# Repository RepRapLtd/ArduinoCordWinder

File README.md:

An Arduino-controlled cord winder for moving things.

(Original application - release chickens from their coop at dawn.)

This consists of a laser-cut box held together with 3D pronted parts.  Inside is a cylindrical winder driven by a geared motor.  These are controlled by an Arduino Uno with a shield that drives the motor.

As distributed it is powered by 12 volts, and takes an opto-isolated input from a solar cell (assumed also to be charging the 12 volt battery).  When the solar voltage rises above a threshold the winder runs until a marker on the wound cord triggers a microswitch, causing it to stop.

There are also push buttons to wind and unwind the cord manually.

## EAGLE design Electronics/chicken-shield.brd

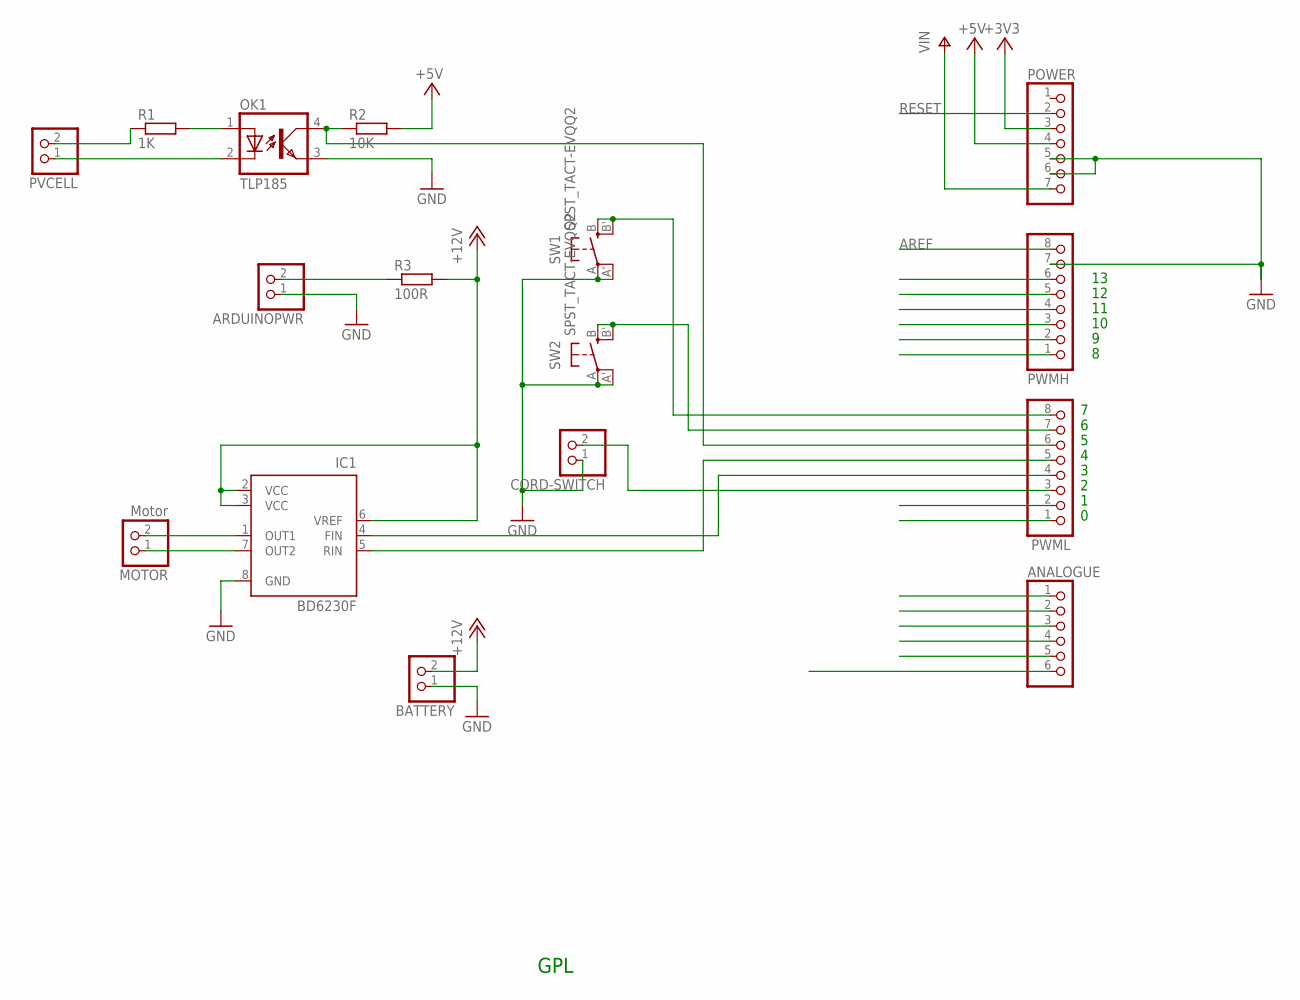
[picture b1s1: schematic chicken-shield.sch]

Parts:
ANALOGUE: PINHD-1X6; 1X06
ARDUINOPWR: PINHD-1X2; 1X02
BATTERY: PINHD-1X2; 1X02
CORD-SWITCH: PINHD-1X2; 1X02
IC1: BD6230F; SOP8
MOTOR: Motor; 1X02
OK1: TLP185; MINI-FLAT-4
POWER: PINHD-1X7; 1X07
PVCELL: PINHD-1X2; 1X02
PWMH: PINHD-1X8; 1X08
PWML: PINHD-1X8; 1X08
R1: 1K; M0805
R2: 10K; M0805
R3: 100R; 0204/7
SW1, SW2: SPST_TACT-EVQQ2; EVQ-Q2

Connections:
+3V3: POWER.3
+5V: POWER.4, R2.2
+12V: BATTERY.2, IC1.2 (VCC), IC1.3 (VCC), IC1.6 (VREF), R3.2
A0: ANALOGUE.1
A1: ANALOGUE.2
A2: ANALOGUE.3
A3: ANALOGUE.4
A4: ANALOGUE.5
A5: ANALOGUE.6
AREF: PWMH.8
DIG0_RX: PWML.1
DIG1_TX: PWML.2
DIG2: IC1.5 (RIN), PWML.5
DIG3: IC1.4 (FIN), PWML.4
DIG4: CORD-SWITCH.2, PWML.3
DIG8: PWMH.1
DIG9: PWMH.2
DIG10: PWMH.3
DIG11: PWMH.4
DIG12: PWMH.5
DIG13: PWMH.6
GND: ARDUINOPWR.1, BATTERY.1, CORD-SWITCH.1, IC1.8 (GND), OK1.3 (EMIT), POWER.5, POWER.6, PWMH.7, SW1.A, SW1.A' (P1), SW2.A, SW2.A' (P1)
unnamed: OK1.2 (C), PVCELL.1
unnamed: OK1.1 (A), R1.2
unnamed: IC1.1 (OUT1), MOTOR.2
unnamed: ARDUINOPWR.2, R3.1
unnamed: IC1.7 (OUT2), MOTOR.1
unnamed: PVCELL.2, R1.1
unnamed: OK1.4 (COL), PWML.6, R2.1
unnamed: PWML.8, SW1.B (S), SW1.B' (S1)
unnamed: PWML.7, SW2.B (S), SW2.B' (S1)
RESET: POWER.2
VIN: POWER.7

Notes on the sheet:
GPL

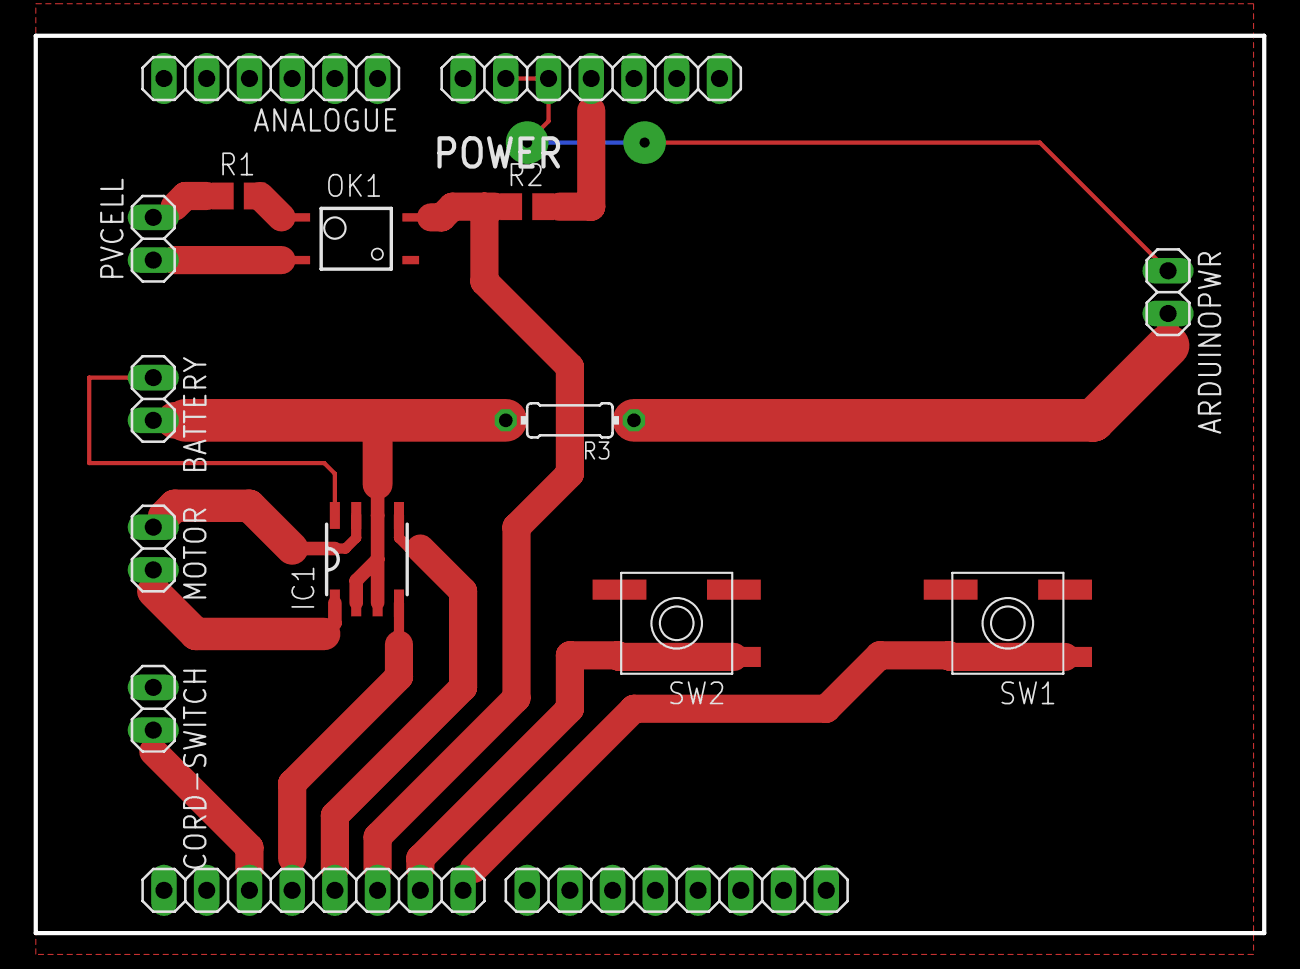
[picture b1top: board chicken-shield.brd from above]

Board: 2 copper layers, 73.0 x 53.3 mm, 16 parts (0 on the bottom side), 15 nets.

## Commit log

2017-06-27 First commit.
2024-05-29 Bringing up to date
